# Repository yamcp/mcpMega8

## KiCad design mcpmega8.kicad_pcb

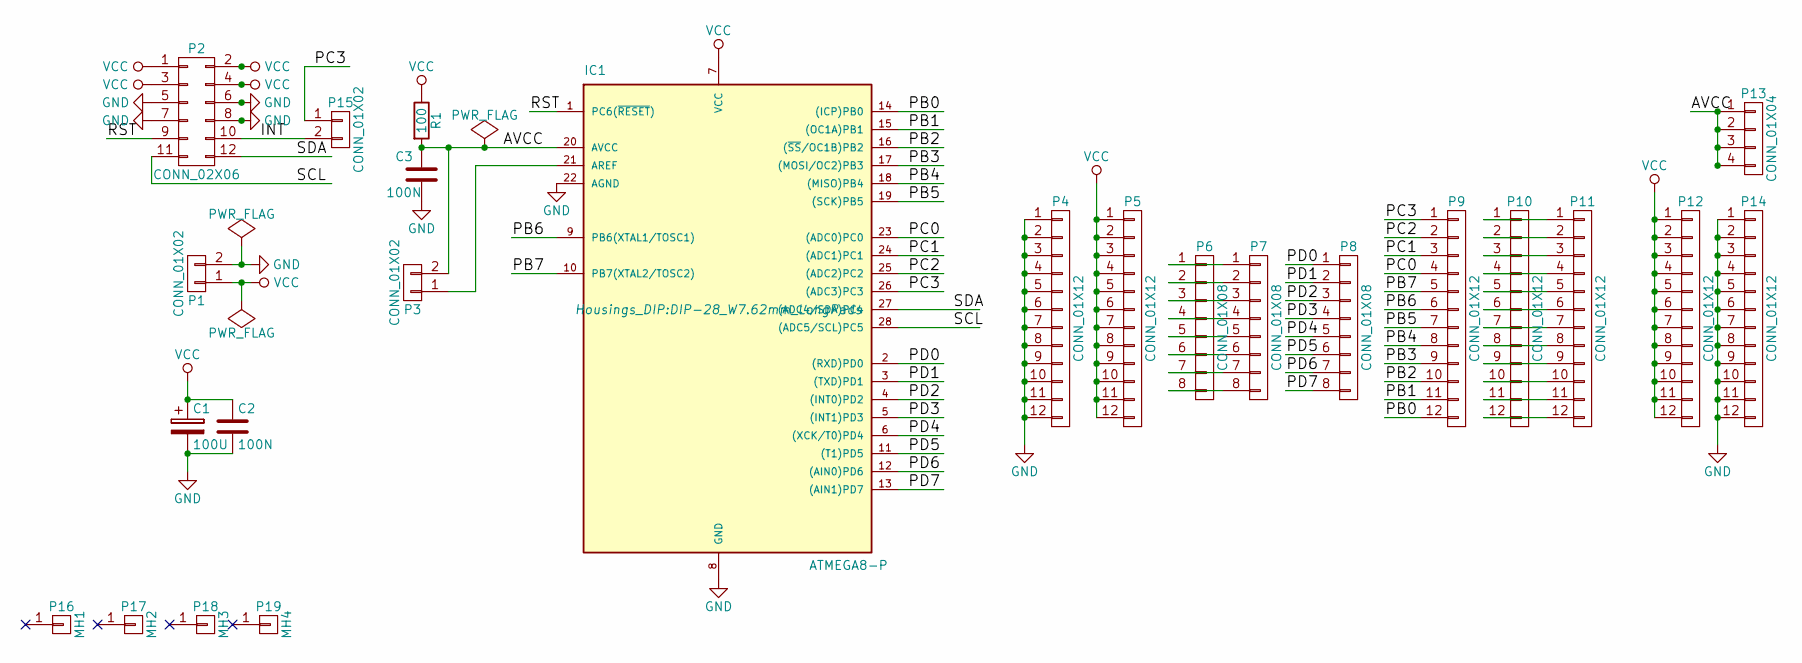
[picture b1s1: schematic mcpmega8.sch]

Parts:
C1: 100U; C_Radial_D5_L11_P2
C2, C3: 100N; C_Rect_L7_W2_P5
IC1: ATMEGA8-P; DIP-28_W7.62mm_LongPads
P1: CONN_01X02; bornier2
P2: CONN_02X06; IDC_Header_Straight_12pins
P3, P15: CONN_01X02; Pin_Header_Straight_1x02
P4, P5, P9, P10, P11, P12, P14: CONN_01X12; Pin_Header_Straight_1x12
P6, P7, P8: CONN_01X08; Pin_Header_Straight_1x08
P13: CONN_01X04; Pin_Header_Straight_1x04
P16: MH1; MountingHole_3-5mm
P17: MH2; MountingHole_3-5mm
P18: MH3; MountingHole_3-5mm
P19: MH4; MountingHole_3-5mm
R1: 100; Resistor_Horizontal_RM10mm

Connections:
/AVCC: C3.1, IC1.20 (AVCC), P3.2, P13.1, P13.2, P13.3, P13.4, R1.2
/INT: P2.10, P15.2
/PB0: IC1.14 ((ICP)PB0), P9.12
/PB1: IC1.15 ((OC1A)PB1), P9.11
/PB2: IC1.16 ((~SS~/OC1B)PB2), P9.10
/PB3: IC1.17 ((MOSI/OC2)PB3), P9.9
/PB4: IC1.18 ((MISO)PB4), P9.8
/PB5: IC1.19 ((SCK)PB5), P9.7
/PB6: IC1.9 (PB6(XTAL1/TOSC1)), P9.6
/PB7: IC1.10 (PB7(XTAL2/TOSC2)), P9.5
/PC0: IC1.23 ((ADC0)PC0), P9.4
/PC1: IC1.24 ((ADC1)PC1), P9.3
/PC2: IC1.25 ((ADC2)PC2), P9.2
/PC3: IC1.26 ((ADC3)PC3), P9.1, P15.1
/PD0: IC1.2 ((RXD)PD0), P8.1
/PD1: IC1.3 ((TXD)PD1), P8.2
/PD2: IC1.4 ((INT0)PD2), P8.3
/PD3: IC1.5 ((INT1)PD3), P8.4
/PD4: IC1.6 ((XCK/T0)PD4), P8.5
/PD5: IC1.11 ((T1)PD5), P8.6
/PD6: IC1.12 ((AIN0)PD6), P8.7
/PD7: IC1.13 ((AIN1)PD7), P8.8
/RST: IC1.1 (PC6(~RESET~)), P2.9
/SCL: IC1.28 ((ADC5/SCL)PC5), P2.11
/SDA: IC1.27 ((ADC4/SDA)PC4), P2.12
GND: C1.2, C2.2, C3.2, IC1.8 (GND), IC1.22 (AGND), P1.2, P2.5, P2.6, P2.7, P2.8, P4.1, P4.2, P4.3, P4.4, P4.5, P4.6, P4.7, P4.8, P4.9, P4.10, P4.11, P4.12, P14.1, P14.2, P14.3, P14.4, P14.5, P14.6, P14.7, P14.8, P14.9, P14.10, P14.11, P14.12
unnamed: IC1.21 (AREF), P3.1
unnamed: P6.1, P7.1
unnamed: P6.2, P7.2
unnamed: P6.3, P7.3
unnamed: P6.4, P7.4
unnamed: P6.5, P7.5
unnamed: P6.6, P7.6
unnamed: P6.7, P7.7
unnamed: P6.8, P7.8
unnamed: P10.1, P11.1
unnamed: P10.2, P11.2
unnamed: P10.3, P11.3
unnamed: P10.4, P11.4
unnamed: P10.5, P11.5
unnamed: P10.6, P11.6
unnamed: P10.7, P11.7
unnamed: P10.8, P11.8
unnamed: P10.9, P11.9
unnamed: P10.10, P11.10
unnamed: P10.11, P11.11
unnamed: P10.12, P11.12
VCC: C1.1, C2.1, IC1.7 (VCC), P1.1, P2.1, P2.2, P2.3, P2.4, P5.1, P5.2, P5.3, P5.4, P5.5, P5.6, P5.7, P5.8, P5.9, P5.10, P5.11, P5.12, P12.1, P12.2, P12.3, P12.4, P12.5, P12.6, P12.7, P12.8, P12.9, P12.10, P12.11, P12.12, R1.1

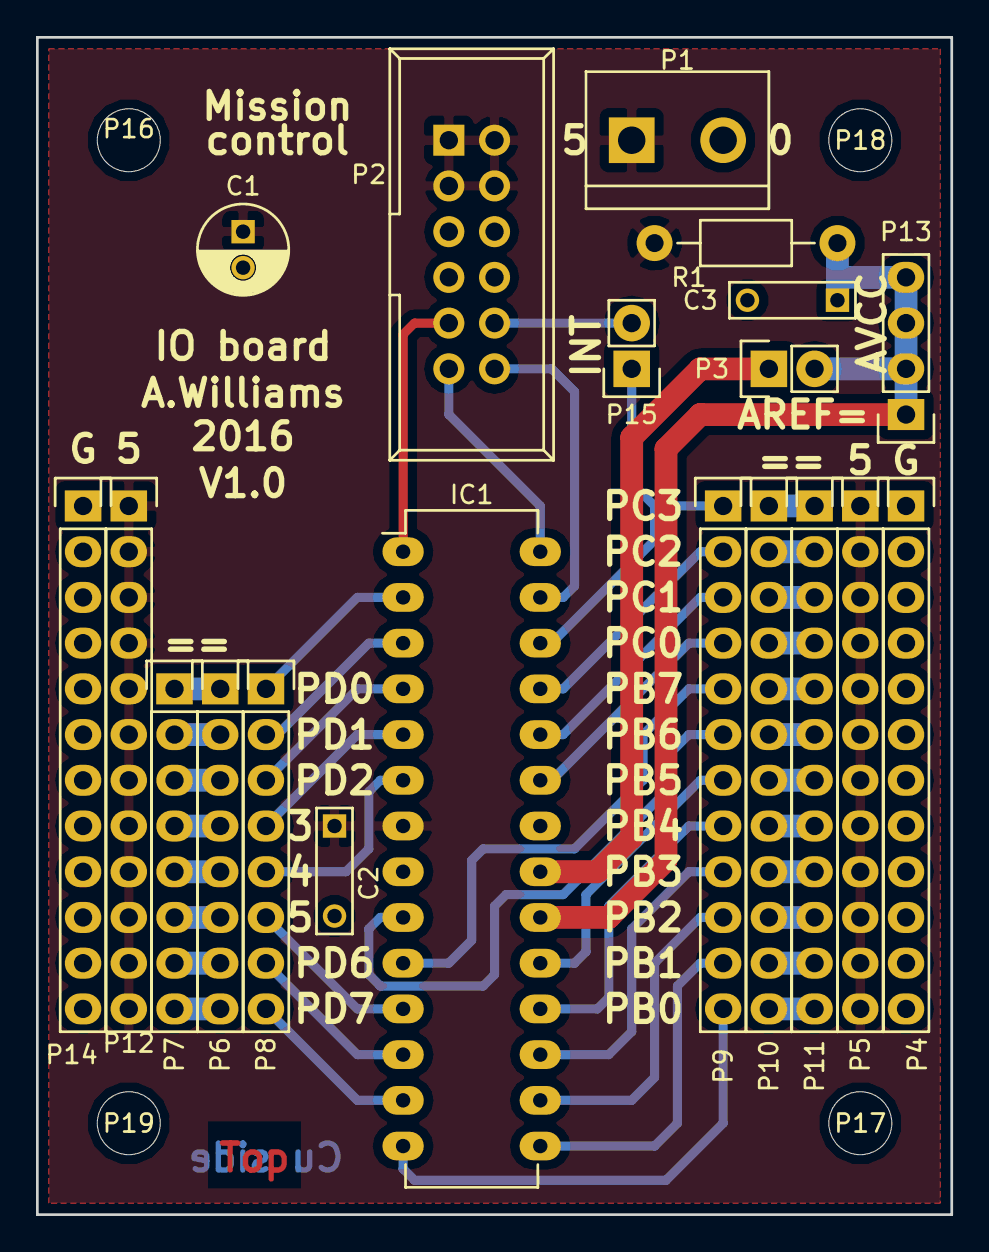
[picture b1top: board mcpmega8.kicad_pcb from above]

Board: 2 copper layers, 50.8 x 65.4 mm, 24 parts (0 on the bottom side), 48 nets.
